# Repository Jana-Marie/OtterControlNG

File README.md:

# OttercontrolNG

Next generation of OtterControl, based on the STM32G431 and STMBL. Increased power density though an aluminum PCB power stage.

(not 100% working/tested yet, firmware to be released soon)

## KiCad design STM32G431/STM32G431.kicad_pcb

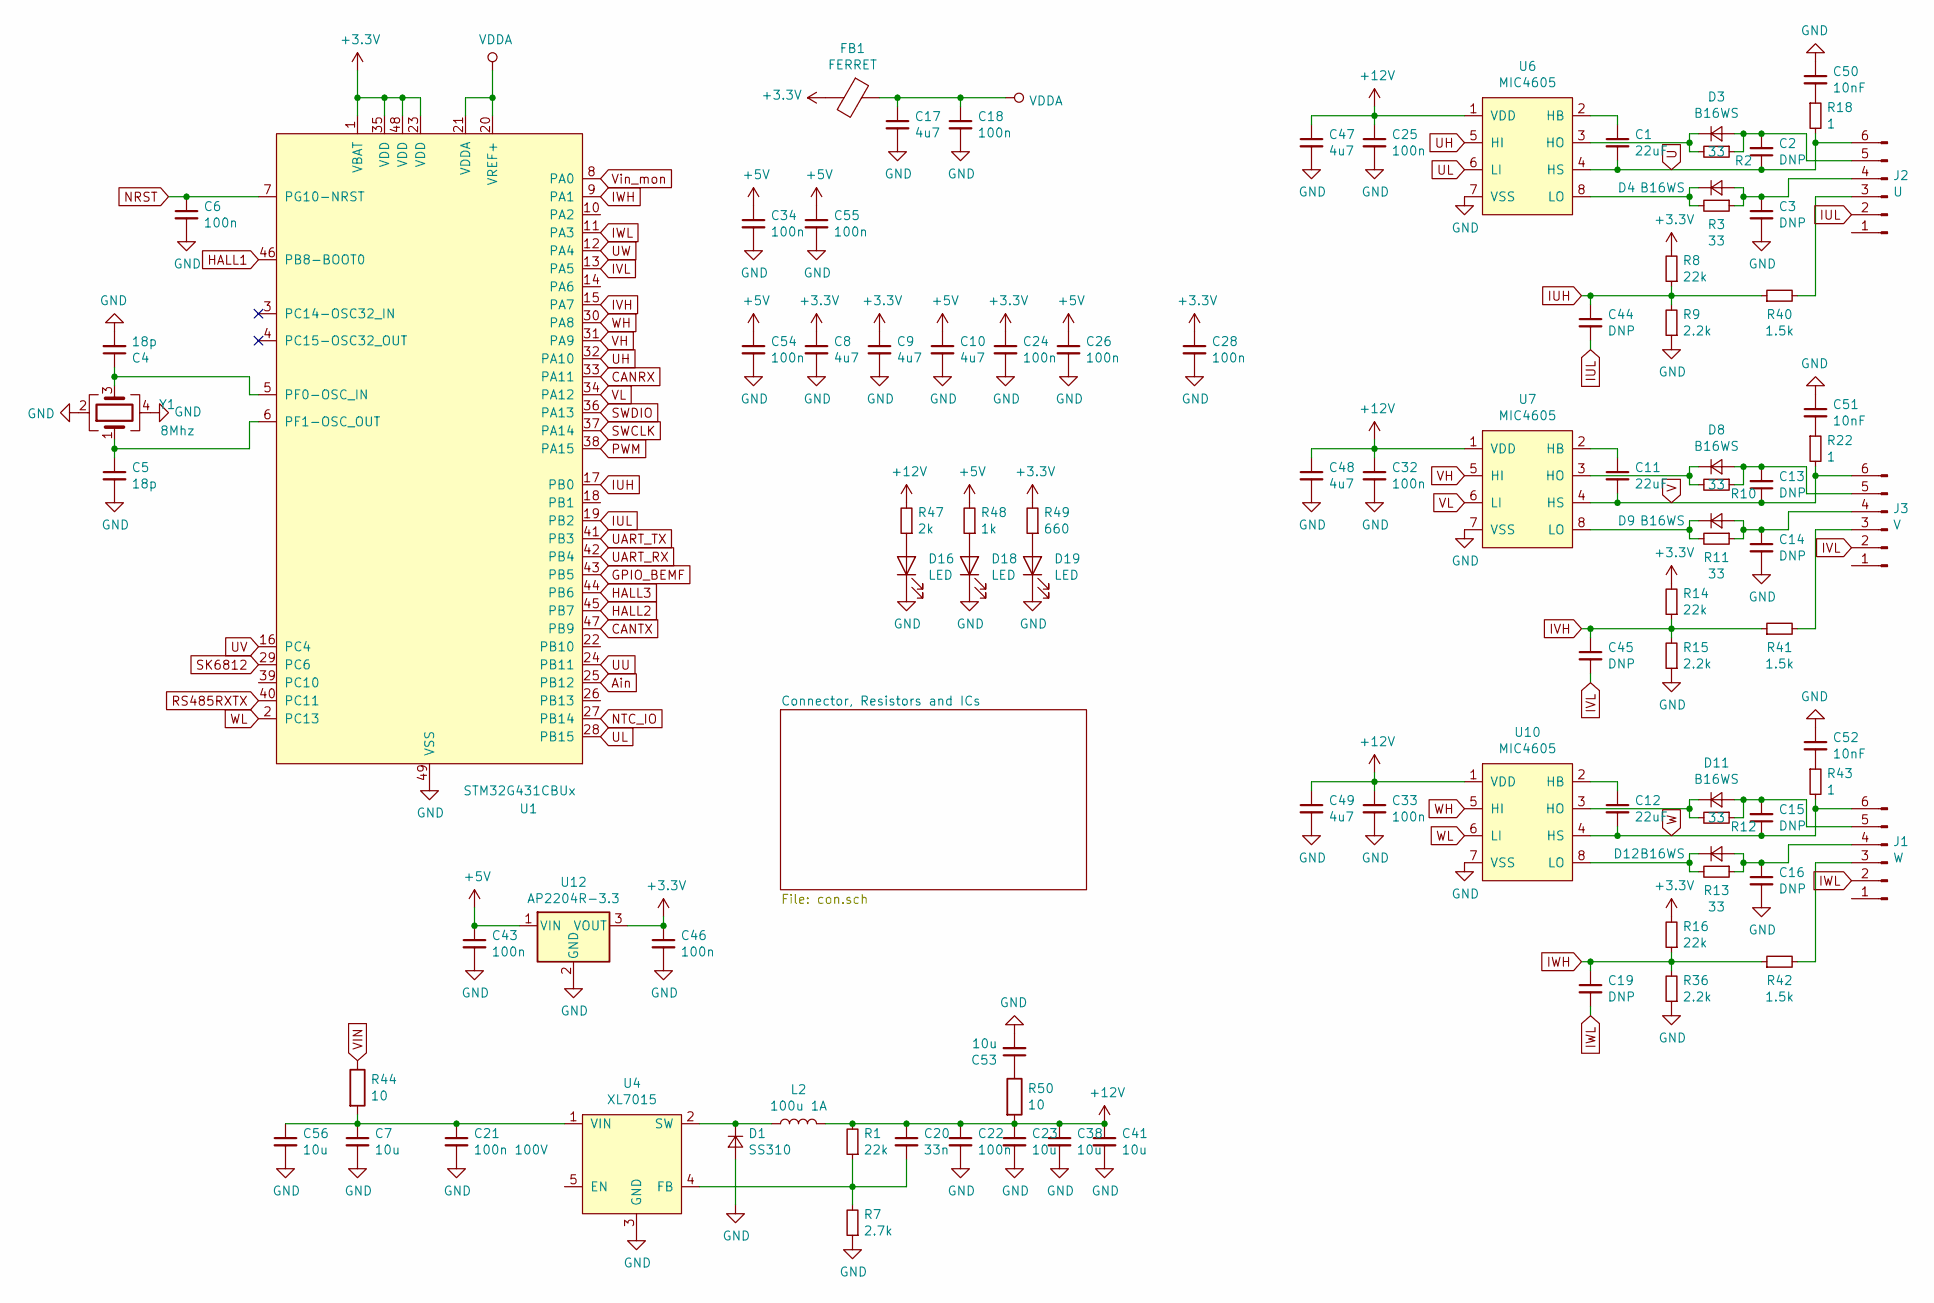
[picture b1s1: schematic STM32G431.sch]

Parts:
C1, C11, C12: 22uF; C_1206_3216Metric
C2, C3, C13, C14, C15, C16: DNP; C_0603_1608Metric
C4, C5: 18p; C_0402_1005Metric
C6, C18, C22, C24, C25, C26, C28, C32, C33, C34, C43, C46, C54, C55: 100n; C_0603_1608Metric
C7, C23, C38, C41, C53, C56: 10u; C_1206_3216Metric
C8, C9, C10, C17, C47, C48, C49: 4u7; C_0603_1608Metric
C19, C44, C45: DNP; C_0402_1005Metric
C20: 33n; C_0402_1005Metric
C21: 100n 100V; C_0603_1608Metric
C50, C51, C52: 10nF; C_0805_2012Metric
D1: SS310; D_SMA; LCSC C14996
D3, D4, D9, D11, D12: B16WS; D_SOD-323
D8: B16WS; D_SOD-323; LCSC C64898
D16, D18, D19: LED; D_0603_1608Metric
FB1: FERRET; L_0805_2012Metric
J1: W; PinHeader_1x06_P2.00mm_Vertical
J2: U; PinHeader_1x06_P2.00mm_Vertical
J3: V; PinHeader_1x06_P2.00mm_Vertical
L2: 100u 1A; L_Taiyo-Yuden_NR-60xx
R1, R8, R14, R16: 22k; R_0402_1005Metric
R2, R3, R10, R11, R12, R13: 33; R_0805_2012Metric
R7: 2.7k; R_0402_1005Metric
R9, R15, R36: 2.2k; R_0402_1005Metric
R18, R22, R43: 1; R_0603_1608Metric
R40, R41, R42: 1.5k; R_0402_1005Metric
R44, R50: 10; R_1206_3216Metric
R47: 2k; R_0603_1608Metric
R48: 1k; R_0603_1608Metric
R49: 660; R_0603_1608Metric
U1: STM32G431CBUx; QFN-48-1EP_7x7mm_P0.5mm_EP5.3x5.3mm
U4: XL7015; TO-252-5_TabPin3
U6, U7, U10: MIC4605; SOIC-8_3.9x4.9mm_P1.27mm
U12: AP2204R-3.3; SOT-89-3
Y1: 8Mhz; Crystal_SMD_3225-4Pin_3.2x2.5mm

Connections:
+3V3: C8.1, C9.1, C24.1, C28.1, C46.1, FB1.2, R8.2, R14.2, R16.2, R49.2, U1.1 (VBAT), U1.23 (VDD), U1.35 (VDD), U1.48 (VDD), U12.3 (VOUT); also elsewhere on the board
+5V: C10.1, C26.1, C34.1, C43.1, C54.1, C55.1, R48.2, U12.1 (VIN); also elsewhere on the board
+12V: C20.1, C22.1, C23.1, C25.1, C32.1, C33.1, C38.1, C41.1, C47.1, C48.1, C49.1, L2.2, R1.2, R47.2, R50.2, U6.1 (VDD), U7.1 (VDD), U10.1 (VDD); also elsewhere on the board
Ain: U1.25 (PB12); also elsewhere on the board
CANRX: U1.33 (PA11); also elsewhere on the board
CANTX: U1.47 (PB9); also elsewhere on the board
GND: C3.2, C4.2, C5.2, C6.2, C7.2, C8.2, C9.2, C10.2, C14.2, C16.2, C17.2, C18.2, C21.2, C22.2, C23.2, C24.2, C25.2, C26.2, C28.2, C32.2, C33.2, C34.2, C38.2, C41.2, C43.2, C46.2, C47.2, C48.2, C49.2, C50.1, C51.1, C52.1, C53.2, C54.2, C55.2, C56.2, D1.2 (A), D16.1 (K), D18.1 (K), D19.1 (K), R7.1, R9.1, R15.1, R36.1, U1.49 (VSS), U4.3 (GND), U6.7 (VSS), U7.7 (VSS), U10.7 (VSS), U12.2 (GND), Y1.2, Y1.4; also elsewhere on the board
GPIO_BEMF: U1.43 (PB5); also elsewhere on the board
HALL1: U1.46 (PB8-BOOT0); also elsewhere on the board
HALL2: U1.45 (PB7); also elsewhere on the board
HALL3: U1.44 (PB6); also elsewhere on the board
IUH: C44.1, R8.1, R9.2, R40.1, U1.17 (PB0)
IUL: C44.2, J2.2, U1.19 (PB2)
IVH: C45.1, R14.1, R15.2, R41.1, U1.15 (PA7)
IVL: C45.2, J3.2, U1.13 (PA5)
IWH: C19.1, R16.1, R36.2, R42.1, U1.9 (PA1)
IWL: C19.2, J1.2, U1.11 (PA3)
NRST: C6.1, U1.7 (PG10-NRST)
NTC_IO: U1.27 (PB14); also elsewhere on the board
unnamed: C1.1, U6.2 (HB)
unnamed: C2.2, D3.2 (A), J2.5, R2.1
unnamed: C3.1, D4.2 (A), J2.4, R3.1
unnamed: C4.1, U1.5 (PF0-OSC_IN), Y1.3
unnamed: C5.1, U1.6 (PF1-OSC_OUT), Y1.1
unnamed: C11.1, U7.2 (HB)
unnamed: C12.1, U10.2 (HB)
unnamed: C13.2, D8.2 (A), J3.5, R10.1
unnamed: C14.1, D9.2 (A), J3.4, R11.1
unnamed: C15.2, D11.2 (A), J1.5, R12.1
unnamed: C16.1, D12.2 (A), J1.4, R13.1
unnamed: C20.2, R1.1, R7.2, U4.4 (FB)
unnamed: C7.1, C21.1, C56.1, R44.2, U4.1 (VIN)
unnamed: C50.2, R18.1
unnamed: C51.2, R22.1
unnamed: C52.2, R43.1
unnamed: C53.1, R50.1
unnamed: D1.1 (K), L2.1, U4.2 (SW)
unnamed: D3.1 (K), R2.2, U6.3 (HO)
unnamed: D4.1 (K), R3.2, U6.8 (LO)
unnamed: D8.1 (K), R10.2, U7.3 (HO)
unnamed: D9.1 (K), R11.2, U7.8 (LO)
unnamed: D11.1 (K), R12.2, U10.3 (HO)
unnamed: D12.1 (K), R13.2, U10.8 (LO)
unnamed: D16.2 (A), R47.1
unnamed: D18.2 (A), R48.1
unnamed: D19.2 (A), R49.1
unnamed: J1.3, R42.2
unnamed: J2.3, R40.2
unnamed: J3.3, R41.2
PWM: U1.38 (PA15); also elsewhere on the board
RS485RXTX: U1.40 (PC11); also elsewhere on the board
SK6812: U1.29 (PC6); also elsewhere on the board
SWCLK: U1.37 (PA14); also elsewhere on the board
SWDIO: U1.36 (PA13); also elsewhere on the board
U: C1.2, C2.1, J2.6, R18.2, U6.4 (HS); also elsewhere on the board
UART_RX: U1.42 (PB4); also elsewhere on the board
UART_TX: U1.41 (PB3); also elsewhere on the board
UH: U1.32 (PA10), U6.5 (HI)
UL: U1.28 (PB15), U6.6 (LI)
UU: U1.24 (PB11); also elsewhere on the board
UV: U1.16 (PC4); also elsewhere on the board
UW: U1.12 (PA4); also elsewhere on the board
V: C11.2, C13.1, J3.6, R22.2, U7.4 (HS); also elsewhere on the board
VDDA: C17.1, C18.1, FB1.1, U1.20 (VREF+), U1.21 (VDDA)
VH: U1.31 (PA9), U7.5 (HI)
VIN: R44.1; also elsewhere on the board
VL: U1.34 (PA12), U7.6 (LI)
Vin_mon: U1.8 (PA0); also elsewhere on the board
W: C12.2, C15.1, J1.6, R43.2, U10.4 (HS); also elsewhere on the board
WH: U1.30 (PA8), U10.5 (HI)
WL: U1.2 (PC13), U10.6 (LI)

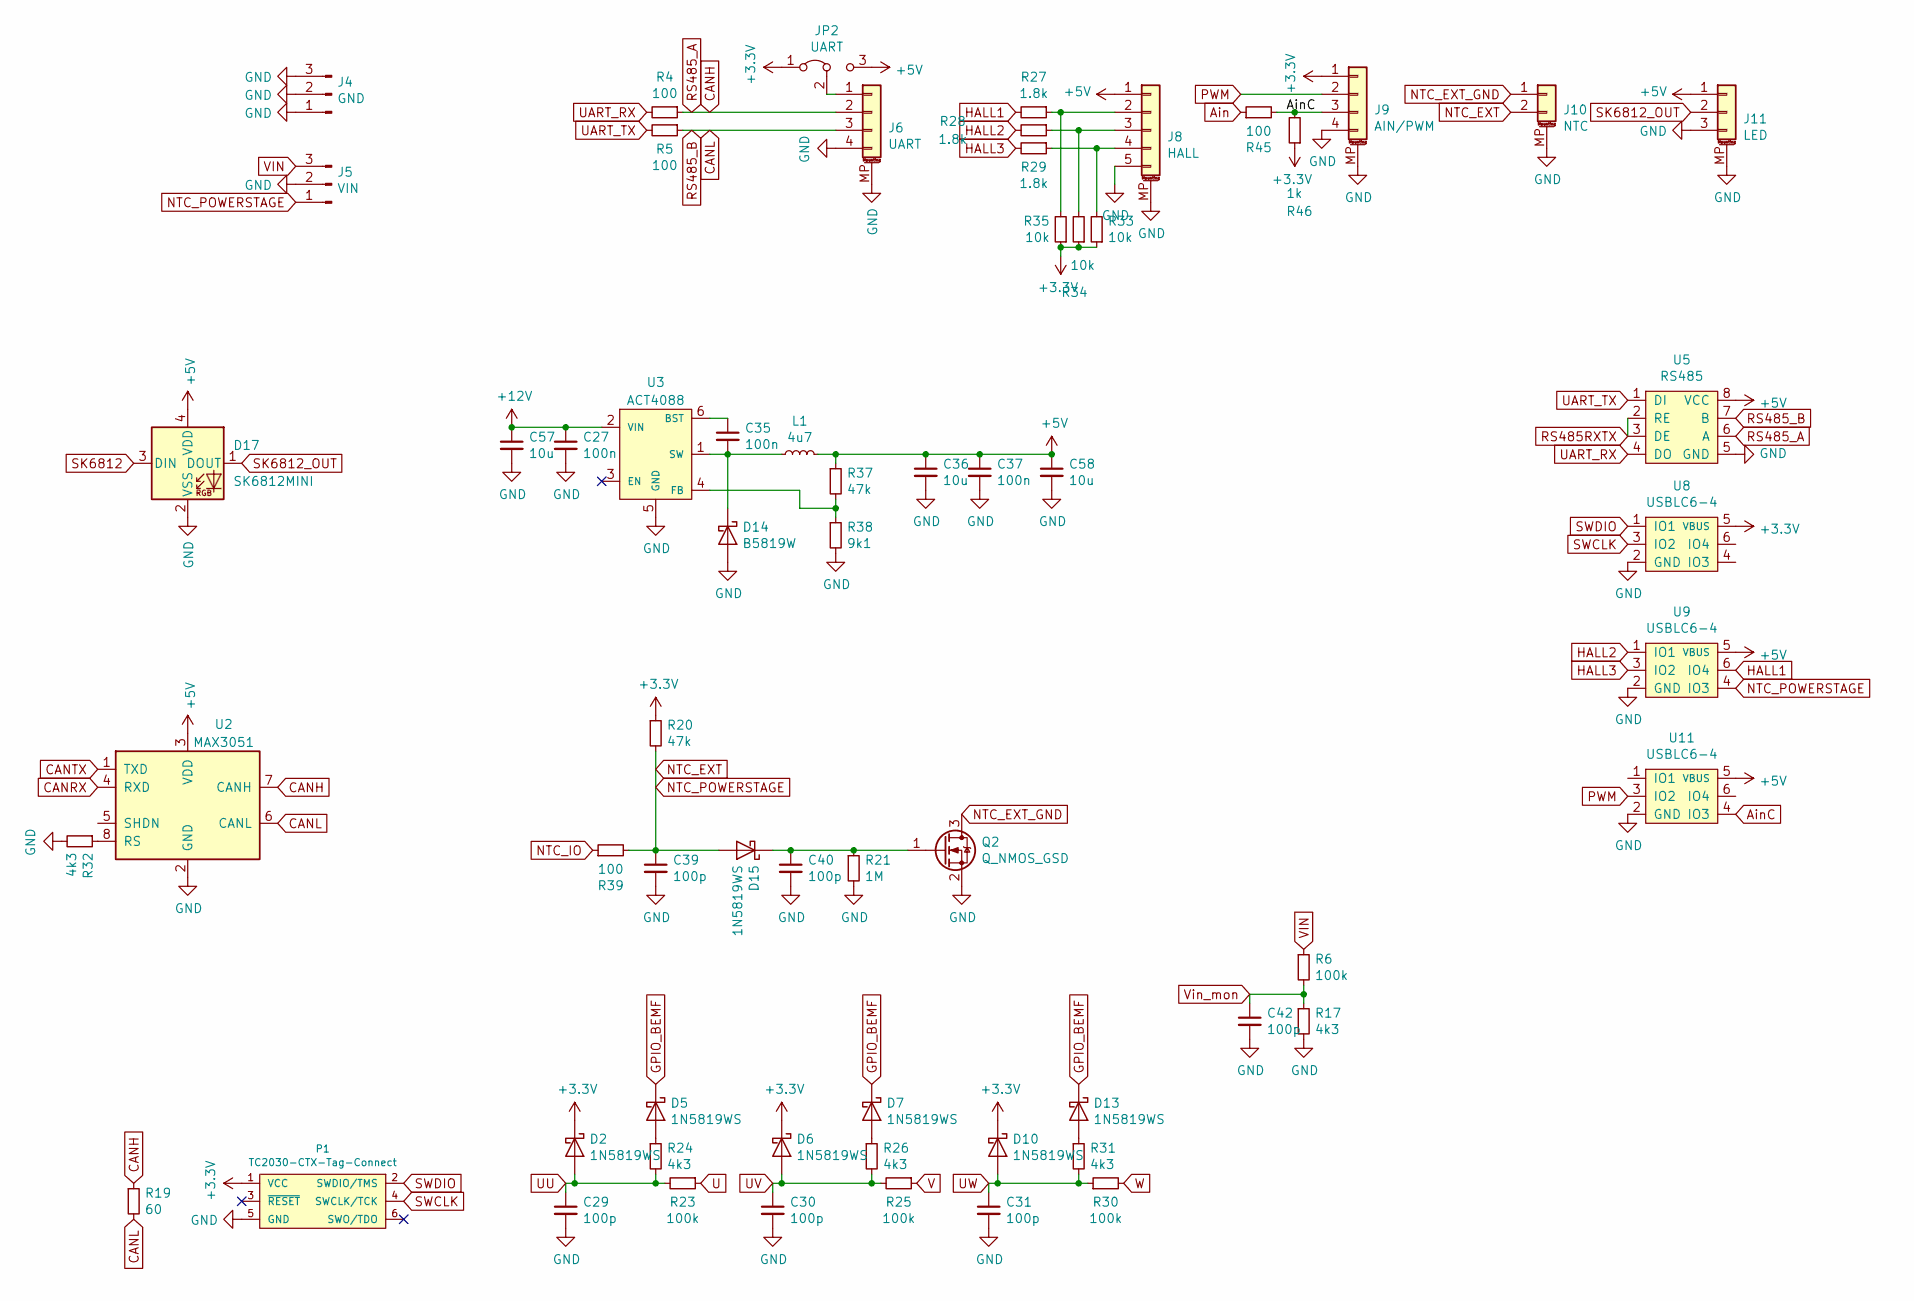
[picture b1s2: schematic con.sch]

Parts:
C27, C35, C37: 100n; C_0603_1608Metric
C29, C30, C31, C42: 100p; C_0402_1005Metric
C36, C57, C58: 10u; C_1206_3216Metric
C39, C40: 100p; R_0402_1005Metric
D2, D5, D6, D7, D10, D13, D15: 1N5819WS; D_SOD-323; LCSC C8598
D14: B5819W; D_SOD-123; LCSC C8598
D17: SK6812MINI; LED_SK6812MINI_PLCC4_3.5x3.5mm_P1.75mm
J4: GND; PinHeader_1x03_P2.00mm_Vertical_COMBI
J5: VIN; PinHeader_1x03_P2.00mm_Vertical_COMBI
J6: UART; Molex_PicoBlade_53261-0471_1x04-1MP_P1.25mm_Horizontal
J8: HALL; Molex_PicoBlade_53261-0571_1x05-1MP_P1.25mm_Horizontal
J9: AIN/PWM; Molex_PicoBlade_53261-0471_1x04-1MP_P1.25mm_Horizontal
J10: NTC; Molex_PicoBlade_53261-0271_1x02-1MP_P1.25mm_Horizontal
J11: LED; Molex_PicoBlade_53261-0371_1x03-1MP_P1.25mm_Horizontal
JP2: UART; SolderJumper-3_P1.3mm_Open_RoundedPad1.0x1.5mm
L1: 4u7; L_Taiyo-Yuden_MD-4040
P1: TC2030-CTX-Tag-Connect; TC2030
Q2: Q_NMOS_GSD; SOT-23
R4, R5, R39, R45: 100; R_0402_1005Metric
R6: 100k; C_0402_1005Metric
R17: 4k3; C_0402_1005Metric
R19: 60; R_0603_1608Metric
R20, R37: 47k; R_0402_1005Metric
R21: 1M; R_0402_1005Metric
R23, R25, R30: 100k; R_0402_1005Metric
R24, R26, R31, R32: 4k3; R_0402_1005Metric
R27, R28, R29: 1.8k; R_0603_1608Metric
R33, R34, R35: 10k; R_0603_1608Metric
R38: 9k1; R_0402_1005Metric
R46: 1k; R_0402_1005Metric
U2: MAX3051; SOIC-8_3.9x4.9mm_P1.27mm
U3: ACT4088; SOT-23-6
U5: RS485; SOIC-8_3.9x4.9mm_P1.27mm
U8, U9, U11: USBLC6-4; SOT-23-6

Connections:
+3V3: D2.1 (K), D6.1 (K), D10.1 (K), J9.1, JP2.1 (A), P1.1 (VCC), R20.1, R33.1, R34.1, R35.1, R46.1, U8.5 (VBUS); also elsewhere on the board
+5V: C36.1, C37.1, C58.1, D17.4 (VDD), J8.1, J11.1, JP2.3 (B), L1.2, R37.1, U2.3 (VDD), U5.8 (VCC), U9.5 (VBUS), U11.5 (VBUS); also elsewhere on the board
+12V: C27.1, C57.1, U3.2 (VIN); also elsewhere on the board
Ain: R45.1; also elsewhere on the board
AinC: J9.3, R45.2, R46.2, U11.4 (IO3)
CANH: J6.2, R4.1, R19.1, U2.7 (CANH), U5.6 (A)
CANL: J6.3, R5.1, R19.2, U2.6 (CANL), U5.7 (B)
CANRX: U2.4 (RXD); also elsewhere on the board
CANTX: U2.1 (TXD); also elsewhere on the board
GND: C27.2, C29.2, C30.2, C31.2, C36.2, C37.2, C39.2, C40.2, C42.2, C57.2, C58.2, D14.2 (A), D17.2 (VSS), J4.1, J4.2, J4.3, J5.2, J6.4, J6.MP (MountPin), J8.5, J8.MP (MountPin), J9.4, J9.MP (MountPin), J10.MP (MountPin), J11.3, J11.MP (MountPin), P1.5 (GND), Q2.2 (S), R17.2, R21.2, R32.2, R38.2, U2.2 (GND), U3.5 (GND), U5.5 (GND), U8.2 (GND), U9.2 (GND), U11.2 (GND); also elsewhere on the board
GPIO_BEMF: D5.1 (K), D7.1 (K), D13.1 (K); also elsewhere on the board
HALL1: R27.2, U9.6 (IO4); also elsewhere on the board
HALL2: R28.2, U9.1 (IO1); also elsewhere on the board
HALL3: R29.2, U9.3 (IO2); also elsewhere on the board
NTC_EXT: C39.1, D15.2 (A), J5.1, J10.2, R20.2, R39.2, U9.4 (IO3)
NTC_EXT_GND: J10.1, Q2.3 (D)
NTC_IO: R39.1; also elsewhere on the board
unnamed: C35.1, U3.6 (BST)
unnamed: C35.2, D14.1 (K), L1.1, U3.1 (SW)
unnamed: C40.1, D15.1 (K), Q2.1 (G), R21.1
unnamed: D5.2 (A), R24.1
unnamed: D7.2 (A), R26.1
unnamed: D13.2 (A), R31.1
unnamed: J6.1, JP2.2 (C)
unnamed: J8.2, R27.1, R35.2
unnamed: J8.3, R28.1, R34.2
unnamed: J8.4, R29.1, R33.2
unnamed: R32.1, U2.8 (RS)
unnamed: R37.2, R38.1, U3.4 (FB)
PWM: J9.2, U11.3 (IO2); also elsewhere on the board
RS485RXTX: U5.2 (RE), U5.3 (DE); also elsewhere on the board
SK6812: D17.3 (DIN); also elsewhere on the board
SK6812_OUT: D17.1 (DOUT), J11.2
SWCLK: P1.4 (SWCLK/TCK), U8.3 (IO2); also elsewhere on the board
SWDIO: P1.2 (SWDIO/TMS), U8.1 (IO1); also elsewhere on the board
U: R23.1; also elsewhere on the board
UART_RX: R4.2, U5.4 (DO); also elsewhere on the board
UART_TX: R5.2, U5.1 (DI); also elsewhere on the board
UU: C29.1, D2.2 (A), R23.2, R24.2; also elsewhere on the board
UV: C30.1, D6.2 (A), R25.2, R26.2; also elsewhere on the board
UW: C31.1, D10.2 (A), R30.1, R31.2; also elsewhere on the board
V: R25.1; also elsewhere on the board
VIN: J5.3, R6.1; also elsewhere on the board
Vin_mon: C42.1, R6.2, R17.1; also elsewhere on the board
W: R30.2; also elsewhere on the board

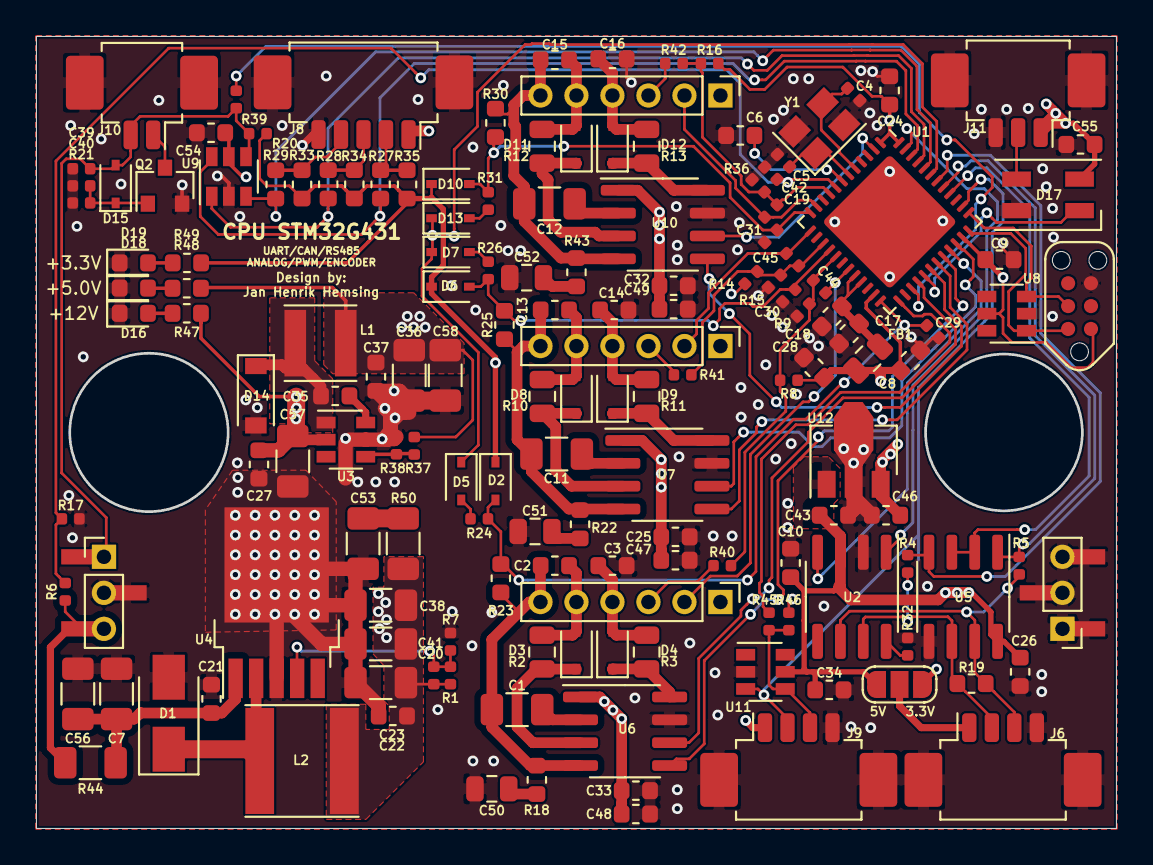
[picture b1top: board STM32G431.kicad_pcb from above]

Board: 4 copper layers, 59.9 x 43.9 mm, 156 parts (0 on the bottom side), 89 nets.

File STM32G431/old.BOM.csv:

Comment,Designator,Footprint, LCSC,
22uF,"C1,C11,C12",Capacitor_SMD:C_0805_2012Metric,C45783,
4u7,"C10,C9,C8,C17,C49,C48,C47",Capacitor_SMD:C_0603_1608Metric,C19666,
100p,"C19,C45,C44,C31,C30,C29,C39,C40,C42",Capacitor_SMD:C_0603_1608Metric,C14858,
DNP,"C2,C3,C13,C14,C15,C16",Capacitor_SMD:C_0603_1608Metric,dnp,
33n,C20,Capacitor_SMD:C_0603_1608Metric,C21117,
100n 100V,C21,Capacitor_SMD:C_0603_1608Metric,,To-source
10u,"C23,C38,C41,C53,C36",Capacitor_SMD:C_1206_3216Metric,C13585,
100n,"C28,C26,C24,C18,C6,C25,C32,C33,C27,C37,C35,C22,C43,C46",Capacitor_SMD:C_0603_1608Metric,C14663,
18p,"C5,C4",Capacitor_SMD:C_0603_1608Metric,C1647,
10nF,"C50,C51,C52",Capacitor_SMD:C_0805_2012Metric,C1710,
100u 100V,C7,Capacitor_THT:CP_Radial_D8.0mm_P3.80mm,C106678,
SS310,D1,Diode_SMD:D_SMA,C14996,
B5819W,"D10,D13,D6,D7,D2,D5",Diode_SMD:D_SOD-123,C8598,
LED,"D16,D18,D19",Diode_SMD:D_0603_1608Metric,C2286,
SK6812MINI,D17,LED_SMD:LED_SK6812MINI_PLCC4_3.5x3.5mm_P1.75mm,,C114583
SM4007PL,"D3,D4,D8,D11,D12,D9,D14,D15",Diode_SMD:D_SOD-123F,C64898,
FERRET,FB1,Inductor_SMD:L_0805_2012Metric,C1015,
W,J1,otter:PinHeader_1x06_P2.00mm_Vertical_COMBI,,To-source
NTC,J10,Connector_Molex:Molex_PicoBlade_53261-0271_1x02-1MP_P1.25mm_Horizontal,,lcsc
LED,J11,Connector_Molex:Molex_PicoBlade_53261-0371_1x03-1MP_P1.25mm_Horizontal,,lcsc
U,J2,otter:PinHeader_1x06_P2.00mm_Vertical_COMBI,,To-source
V,J3,otter:PinHeader_1x06_P2.00mm_Vertical_COMBI,,To-source
GND,J4,otter:PinHeader_1x03_P2.00mm_Vertical_COMBI,,To-source
VIN,J5,otter:PinHeader_1x03_P2.00mm_Vertical_COMBI,,To-source
UART,J6,Connector_Molex:Molex_PicoBlade_53261-0471_1x04-1MP_P1.25mm_Horizontal,,lcsc
HALL,J8,Connector_Molex:Molex_PicoBlade_53261-0571_1x05-1MP_P1.25mm_Horizontal,,lcsc
AIN/PWM,J9,Connector_Molex:Molex_PicoBlade_53261-0471_1x04-1MP_P1.25mm_Horizontal,,lcsc
UART,JP2,Jumper:SolderJumper-3_P1.3mm_Open_RoundedPad1.0x1.5mm,dnp,
4u7,L1,Inductor_SMD:L_Taiyo-Yuden_MD-4040,,lcsc
100u 1A,L2,Inductor_SMD:L_Taiyo-Yuden_MD-5050,,lcsc
TC2030-CTX-Tag-Connect,P1,otter:TC2030,dnp,
Q_NMOS_GSD,Q2,Package_TO_SOT_SMD:SOT-23,C8545,
22k,"R16,R14,R8,R1",Resistor_SMD:R_0603_1608Metric,C31850,
1,"R18,R22,R43",Resistor_SMD:R_0603_1608Metric,C22936,
60,R19,Resistor_SMD:R_0603_1608Metric,dnp,
2,"R2,R3,R10,R11,R12,R13",Resistor_SMD:R_0805_2012Metric,C17606,
47k,"R20,R37",Resistor_SMD:R_0603_1608Metric,C25819,
1M,R21,Resistor_SMD:R_0603_1608Metric,C22935,
1.8k,"R28,R27,R29",Resistor_SMD:R_0603_1608Metric,C4177,
100k,"R30,R25,R23,R6",Resistor_SMD:R_0603_1608Metric,C25803,
4k3,"R31,R24,R17,R32,R26",Resistor_SMD:R_0603_1608Metric,C23159,
10k,"R35,R34,R33",Resistor_SMD:R_0603_1608Metric,C25804,
2.2k,"R36,R15,R9",Resistor_SMD:R_0603_1608Metric,C4190,
9k1,R38,Resistor_SMD:R_0603_1608Metric,C23260,
100,"R39,R5,R4,R45",Resistor_SMD:R_0603_1608Metric,C22775,
1.5k,"R42,R41,R40",Resistor_SMD:R_0603_1608Metric,C22843,
10,"R44,R50",Resistor_SMD:R_1206_3216Metric,C17903,
2k,R47,Resistor_SMD:R_0603_1608Metric,C22975,
1k,"R48,R46",Resistor_SMD:R_0603_1608Metric,C21190,
660,R49,Resistor_SMD:R_0603_1608Metric,C23228,
2.7k,R7,Resistor_SMD:R_0603_1608Metric,C13167,
STM32G431CBUx,U1,Package_DFN_QFN:QFN-48-1EP_6x6mm_P0.4mm_EP4.2x4.2mm,,To-source
AMS1117-3.3,U12,Package_TO_SOT_SMD:SOT-223-3_TabPin2,C6186,
MAX3051,U2,Package_SO:SOIC-8_3.9x4.9mm_P1.27mm,dnp,
ACT4088,U3,Package_TO_SOT_SMD:SOT-23-6,,niklas
XL7015,U4,Package_TO_SOT_SMD:TO-252-5_TabPin3,C73013,
RS485,U5,Package_SO:SOIC-8_3.9x4.9mm_P1.27mm,dnp,
MIC4605,"U7,U10,U6",Package_SO:SOIC-8_3.9x4.9mm_P1.27mm,,niklas
USBLC6-4,"U8,U11,U9",Package_TO_SOT_SMD:SOT-23-6,C252436,
8Mhz,Y1,Crystal:Crystal_SMD_3225-4Pin_3.2x2.5mm,C57131,

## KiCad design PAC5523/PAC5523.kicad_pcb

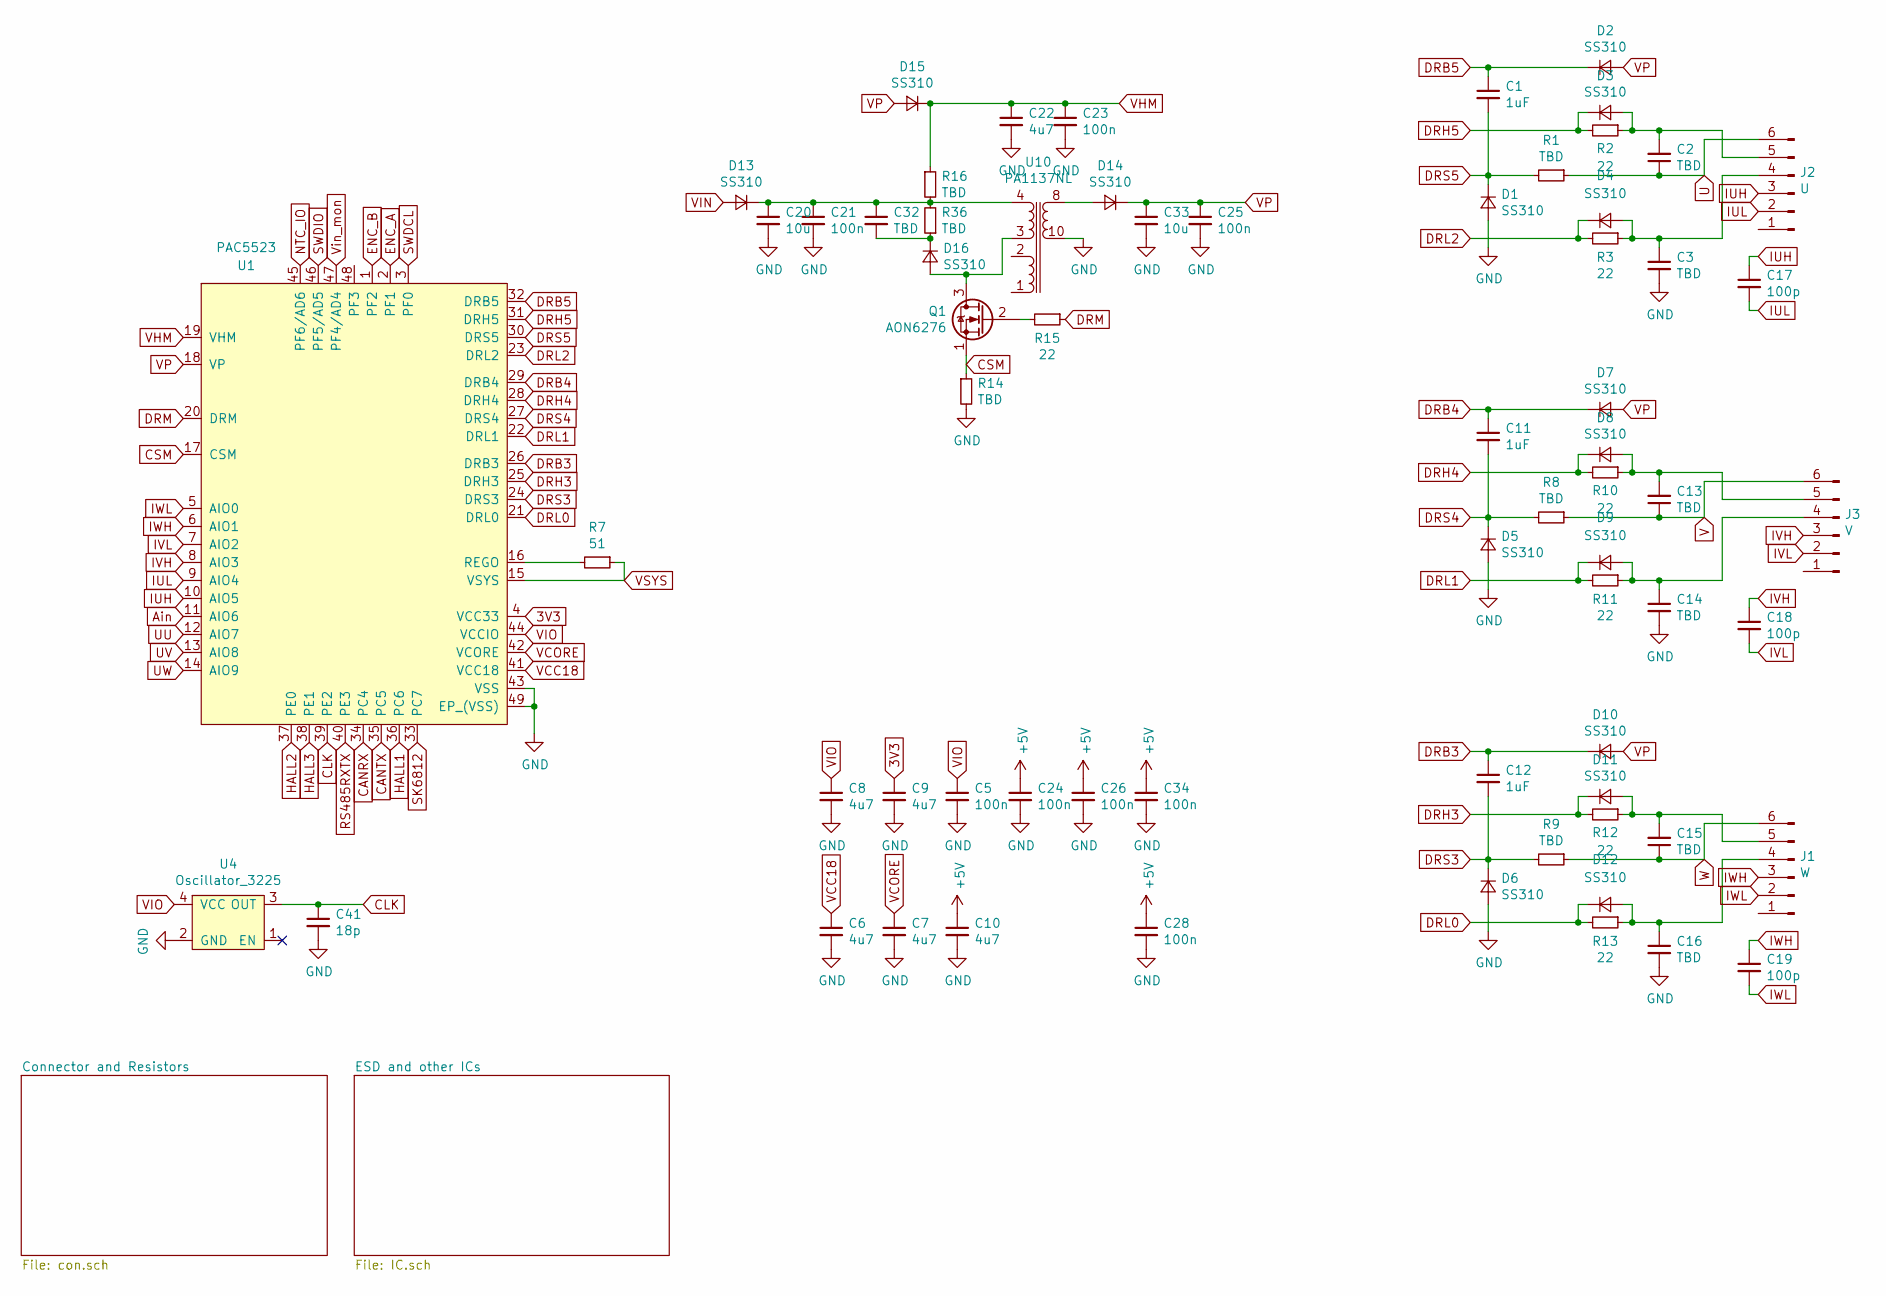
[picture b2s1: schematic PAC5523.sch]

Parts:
C1, C11, C12: 1uF; C_0805_2012Metric
C2, C3, C13, C14, C15, C16, C32: TBD; C_0603_1608Metric
C5, C21, C23, C24, C25, C26, C28, C34: 100n; C_0603_1608Metric
C6, C7, C8, C9, C10, C22: 4u7; C_0603_1608Metric
C17, C18, C19: 100p; C_0603_1608Metric
C20, C33: 10u; C_1206_3216Metric
C41: 18p; C_0603_1608Metric
D1, D2, D3, D4, D5, D6, D7, D8, D9, D10, D11, D12, D13, D14, D15, D16: SS310; D_SOD-123F
J1: W; PinHeader_1x06_P2.00mm_Vertical_COMBI
J2: U; PinHeader_1x06_P2.00mm_Vertical_COMBI
J3: V; PinHeader_1x06_P2.00mm_Vertical_COMBI
Q1: AON6276; VSONP-8-1EP_5x6_P1.27mm
R1, R8, R9, R16, R36: TBD; R_0603_1608Metric
R2, R3, R10, R11, R12, R13, R15: 22; R_0805_2012Metric
R7: 51; R_0603_1608Metric
R14: TBD; R_0805_2012Metric
U1: PAC5523; QFN-48-1EP_6x6mm_P0.4mm_EP4.2x4.2mm
U4: Oscillator_3225
U10: PA1137NL

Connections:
3V3: C9.1, U1.4 (VCC33); also elsewhere on the board
+5V: C10.1, C24.1, C26.1, C28.1, C34.1; also elsewhere on the board
Ain: U1.11 (AIO6); also elsewhere on the board
CANRX: U1.34 (PC4); also elsewhere on the board
CANTX: U1.35 (PC5); also elsewhere on the board
CLK: C41.1, U1.39 (PE2), U4.3 (OUT)
CSM: Q1.1 (S), R14.1, U1.17 (CSM)
DRB3: C12.1, D10.1 (K), U1.26 (DRB3)
DRB4: C11.1, D7.1 (K), U1.29 (DRB4)
DRB5: C1.1, D2.1 (K), U1.32 (DRB5)
DRH3: D11.1 (K), R12.2, U1.25 (DRH3)
DRH4: D8.1 (K), R10.2, U1.28 (DRH4)
DRH5: D3.1 (K), R2.2, U1.31 (DRH5)
DRL0: D12.1 (K), R13.2, U1.21 (DRL0)
DRL1: D9.1 (K), R11.2, U1.22 (DRL1)
DRL2: D4.1 (K), R3.2, U1.23 (DRL2)
DRM: R15.1, U1.20 (DRM)
DRS3: C12.2, D6.1 (K), R9.2, U1.24 (DRS3)
DRS4: C11.2, D5.1 (K), R8.2, U1.27 (DRS4)
DRS5: C1.2, D1.1 (K), R1.2, U1.30 (DRS5)
ENC_A: U1.2 (PF1); also elsewhere on the board
ENC_B: U1.1 (PF2); also elsewhere on the board
GND: C3.2, C5.2, C6.2, C7.2, C8.2, C9.2, C10.2, C14.2, C16.2, C20.2, C21.2, C22.2, C23.2, C24.2, C25.2, C26.2, C28.2, C33.2, C34.2, C41.2, D1.2 (A), D5.2 (A), D6.2 (A), R14.2, U1.43 (VSS), U1.49 (EP_(VSS)), U4.2 (GND), U10.9, U10.10; also elsewhere on the board
HALL1: U1.36 (PC6); also elsewhere on the board
HALL2: U1.37 (PE0); also elsewhere on the board
HALL3: U1.38 (PE1); also elsewhere on the board
IUH: C17.1, J2.3, U1.10 (AIO5)
IUL: C17.2, J2.2, U1.9 (AIO4)
IVH: C18.1, J3.3, U1.8 (AIO3)
IVL: C18.2, J3.2, U1.7 (AIO2)
IWH: C19.1, J1.3, U1.6 (AIO1)
IWL: C19.2, J1.2, U1.5 (AIO0)
NTC_IO: U1.45 (PF6/AD6); also elsewhere on the board
unnamed: C2.2, D3.2 (A), J2.5, R2.1
unnamed: C3.1, D4.2 (A), J2.4, R3.1
unnamed: C13.2, D8.2 (A), J3.5, R10.1
unnamed: C14.1, D9.2 (A), J3.4, R11.1
unnamed: C15.2, D11.2 (A), J1.5, R12.1
unnamed: C16.1, D12.2 (A), J1.4, R13.1
unnamed: C20.1, C21.1, C32.1, D13.1 (K), R16.2, R36.2, U10.4
unnamed: C32.2, D16.1 (K), R36.1
unnamed: D14.2 (A), U10.7, U10.8
unnamed: D16.2 (A), Q1.3 (D), U10.3
unnamed: Q1.2 (G), R15.2
unnamed: R7.2, U1.16 (REGO)
RS485RXTX: U1.40 (PE3); also elsewhere on the board
SK6812: U1.33 (PC7); also elsewhere on the board
SWDCL: U1.3 (PF0); also elsewhere on the board
SWDIO: U1.46 (PF5/AD5); also elsewhere on the board
U: C2.1, J2.6, R1.1; also elsewhere on the board
UU: U1.12 (AIO7); also elsewhere on the board
UV: U1.13 (AIO8); also elsewhere on the board
UW: U1.14 (AIO9); also elsewhere on the board
V: C13.1, J3.6, R8.1; also elsewhere on the board
VCC18: C6.1, U1.41 (VCC18)
VCORE: C7.1, U1.42 (VCORE)
VHM: C22.1, C23.1, D15.1 (K), R16.1, U1.19 (VHM)
VIN: D13.2 (A); also elsewhere on the board
VIO: C5.1, C8.1, U1.44 (VCCIO), U4.4 (VCC); also elsewhere on the board
VP: C25.1, C33.1, D2.2 (A), D7.2 (A), D10.2 (A), D14.1 (K), D15.2 (A), U1.18 (VP); also elsewhere on the board
VSYS: R7.1, U1.15 (VSYS)
Vin_mon: U1.47 (PF4/AD4); also elsewhere on the board
W: C15.1, J1.6, R9.1; also elsewhere on the board

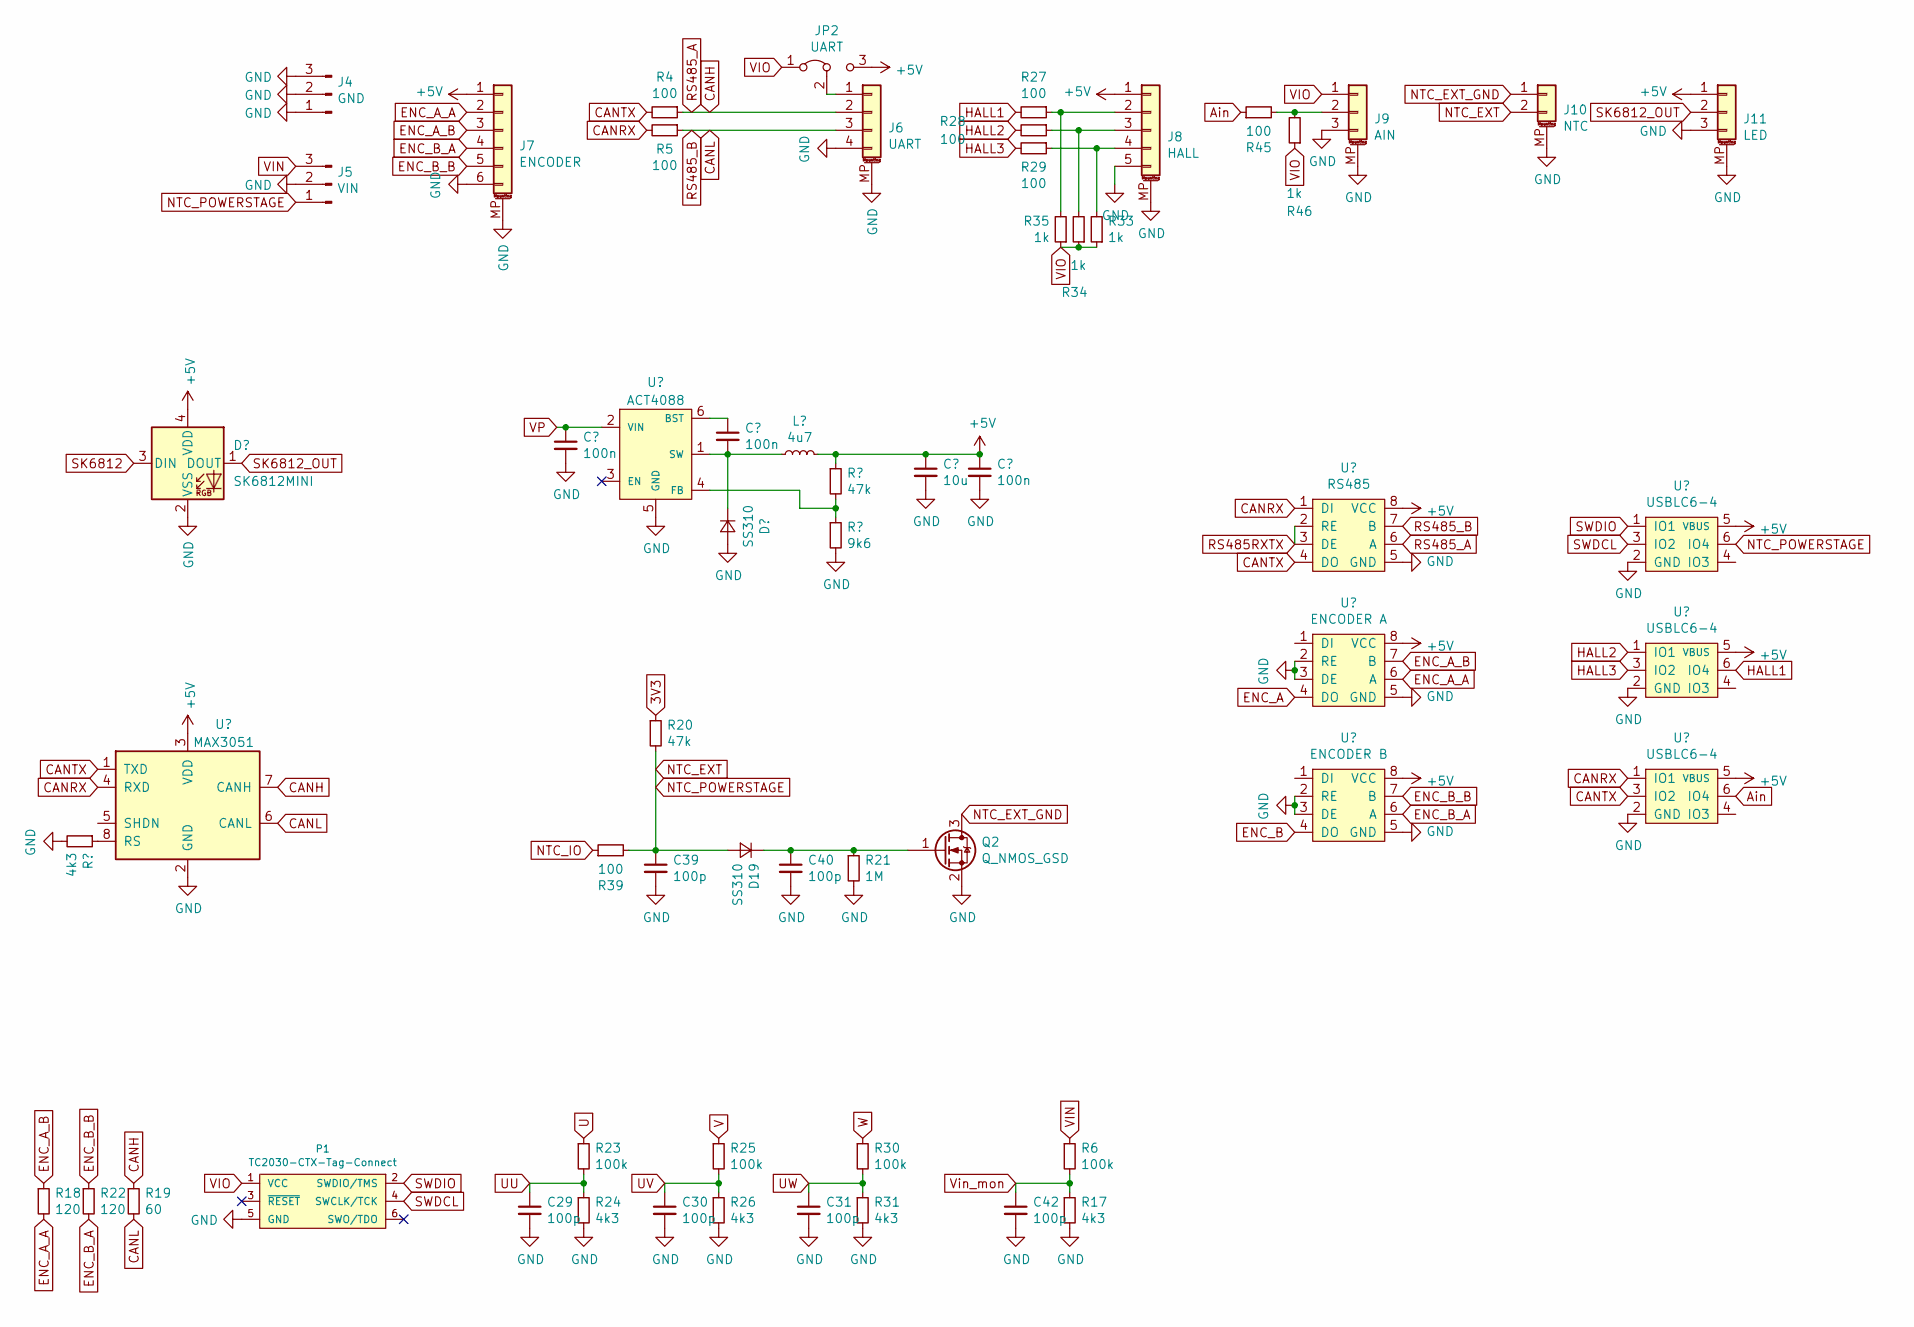
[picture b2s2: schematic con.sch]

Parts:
C29, C30, C31, C39, C40, C42: 100p; C_0603_1608Metric
D19: SS310; D_SOD-123F
J4: GND; PinHeader_1x03_P2.00mm_Vertical_COMBI
J5: VIN; PinHeader_1x03_P2.00mm_Vertical_COMBI
J6: UART; Molex_PicoBlade_53261-0471_1x04-1MP_P1.25mm_Horizontal
J7: ENCODER; Molex_PicoBlade_53261-0671_1x06-1MP_P1.25mm_Horizontal
J8: HALL; Molex_PicoBlade_53261-0571_1x05-1MP_P1.25mm_Horizontal
J9: AIN; Molex_PicoBlade_53261-0371_1x03-1MP_P1.25mm_Horizontal
J10: NTC; Molex_PicoBlade_53261-0271_1x02-1MP_P1.25mm_Horizontal
J11: LED; Molex_PicoBlade_53261-0371_1x03-1MP_P1.25mm_Horizontal
JP2: UART; SolderJumper-3_P1.3mm_Open_RoundedPad1.0x1.5mm
P1: TC2030-CTX-Tag-Connect; TC2030
Q2: Q_NMOS_GSD; SOT-23
R4, R5, R27, R28, R29, R39, R45: 100; R_0603_1608Metric
R6, R23, R25, R30: 100k; R_0603_1608Metric
R17, R24, R26, R31: 4k3; R_0603_1608Metric
R18, R22: 120; R_0603_1608Metric
R19: 60; R_0603_1608Metric
R20: 47k; R_0603_1608Metric
R21: 1M; R_0603_1608Metric
R33, R34, R35, R46: 1k; R_0603_1608Metric

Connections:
3V3: R20.1; also elsewhere on the board
+5V: J7.1, J8.1, J11.1, JP2.3 (B); also elsewhere on the board
Ain: R45.1; also elsewhere on the board
CANH: J6.2, R4.1, R19.1; also elsewhere on the board
CANL: J6.3, R5.1, R19.2; also elsewhere on the board
CANRX: R5.2; also elsewhere on the board
CANTX: R4.2; also elsewhere on the board
ENC_A_A: J7.2, R18.2; also elsewhere on the board
ENC_A_B: J7.3, R18.1; also elsewhere on the board
ENC_B_A: J7.4, R22.2; also elsewhere on the board
ENC_B_B: J7.5, R22.1; also elsewhere on the board
GND: C29.2, C30.2, C31.2, C39.2, C40.2, C42.2, J4.1, J4.2, J4.3, J5.2, J6.4, J6.MP (MountPin), J7.6, J7.MP (MountPin), J8.5, J8.MP (MountPin), J9.3, J9.MP (MountPin), J10.MP (MountPin), J11.3, J11.MP (MountPin), P1.5 (GND), Q2.2 (S), R17.2, R21.2, R24.2, R26.2, R31.2; also elsewhere on the board
HALL1: R27.2; also elsewhere on the board
HALL2: R28.2; also elsewhere on the board
HALL3: R29.2; also elsewhere on the board
NTC_EXT: C39.1, D19.2 (A), J5.1, J10.2, R20.2, R39.2; also elsewhere on the board
NTC_EXT_GND: J10.1, Q2.3 (D)
NTC_IO: R39.1; also elsewhere on the board
unnamed: C40.1, D19.1 (K), Q2.1 (G), R21.1
unnamed: J6.1, JP2.2 (C)
unnamed: J8.2, R27.1, R35.2
unnamed: J8.3, R28.1, R34.2
unnamed: J8.4, R29.1, R33.2
unnamed: J9.2, R45.2, R46.2
SK6812_OUT: J11.2; also elsewhere on the board
SWDCL: P1.4 (SWCLK/TCK); also elsewhere on the board
SWDIO: P1.2 (SWDIO/TMS); also elsewhere on the board
U: R23.1; also elsewhere on the board
UU: C29.1, R23.2, R24.1; also elsewhere on the board
UV: C30.1, R25.2, R26.1; also elsewhere on the board
UW: C31.1, R30.2, R31.1; also elsewhere on the board
V: R25.1; also elsewhere on the board
VIN: J5.3, R6.1; also elsewhere on the board
VIO: J9.1, JP2.1 (A), P1.1 (VCC), R33.1, R34.1, R35.1, R46.1; also elsewhere on the board
Vin_mon: C42.1, R6.2, R17.1; also elsewhere on the board
W: R30.1; also elsewhere on the board
